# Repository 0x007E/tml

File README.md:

# `TML` - Temperature Logger

The `TML` is a board with an [LM386](#additional-information) that is used to scale up a temperature (0°-100°) from [KT200](#additional-information). The temperature gets A/D converted over an [ATtiny1606](#additional-information) and is stored in an eeprom [AT24CM0X](#additional-information) with current time and date that is provided by a [MCP7940](#additional-information) r(eal)-t(ime)-c(lock). The board itself provides a reverse polarity protection and can be supplied between `9-12V`. The voltage is line regulated to `5V`.

| Experience | Level |
|:------------|:-----:|
| Soldering   |  |

# Downloads

| Type      | File               | Description              |
|:---------:|:------------------:|:-------------------------|
| Schematic | [pdf](https://github.com/0x007E/tml/releases/latest/download/schematic.pdf) / [cadlab](https://cadlab.io/project/30575/main/files) | Schematic files |
| Board | [pdf](https://github.com/0x007E/tml/releases/latest/download/pcb.pdf) / [cadlab](https://cadlab.io/project/30575/main/files) | Board file |
| Drill | [pdf](https://github.com/0x007E/tml/releases/latest/download/drill.pdf) | Drill file |
| BoM | [xlsx](https://github.com/0x007E/tml/releases/latest/download/bom.xlsx) / [html](https://github.com/0x007E/tml/releases/latest/download/ibom.html)          | Bill of Material as Excel/interactive HTML |
| PCB    | [zip](https://github.com/0x007E/tml/releases/latest/download/kicad.zip) / [tar](https://github.com/0x007E/tml/releases/latest/download/kicad.tar.gz)    | KiCAD/Gerber/BoM/Drill files       |

# Hardware

The pcb is created with `KiCAD`. All files are built with `github actions` so that they are ready for a production environment.

## PCB

The circuit board is populated on both sides (Top, Bottom). The best way for soldering the `SMD` components is within a vapor phase soldering system and for the `THT` components with a standard soldering system.

### Top Layer

### Bottom Layer

# Additional Information

| Type  | Link                                                | Description                                   |
|:------|:---------------------------------------------------:|:----------------------------------------------|
| LM358 | [pdf](https://www.ti.com/lit/ds/symlink/lm358b.pdf) | Industry-Standard Dual Operational Amplifiers |
| KT200 | [pdf](https://rocelec.widen.net/view/pdf/qxp2nqwwr1/INFNS04262-1.pdf?t.download=true&u=5oefqw) | Silicon Temperature Sensors |
| ATtiny1606 | [pdf](https://ww1.microchip.com/downloads/en/DeviceDoc/ATtiny804-06-07-1604-06-07-DataSheet-DS40002312A.pdf) | tinyAVR® 0-series |
| AT24CM01 | [pdf](https://ww1.microchip.com/downloads/en/DeviceDoc/AT24CM01-I2C-Compatible-Two-Wire-Serial-EEPROM-Data-Sheet-20006170A.pdf) | I²C-Compatible (Two-Wire) Serial EEPROM 1‑Mbit (131,072 x 8) |
| AT24CM02 | [pdf](https://ww1.microchip.com/downloads/en/DeviceDoc/I%C2%B2C-Compatible-(Two-Wire)-Serial-EEPROM-2-Mbit-(262,144x8)-20006197B.pdf) | I²C-Compatible (Two-Wire) Serial EEPROM 2‑Mbit (262,144 x 8) |
| MCP7940 | [pdf](https://ww1.microchip.com/downloads/en/DeviceDoc/MCP7940M-Low-Cost%20I2C-RTCC-with-SRAM-20002292C.pdf) | Low-Cost I2C Real-Time Clock/Calendar with SRAM |

---

R. GAECHTER

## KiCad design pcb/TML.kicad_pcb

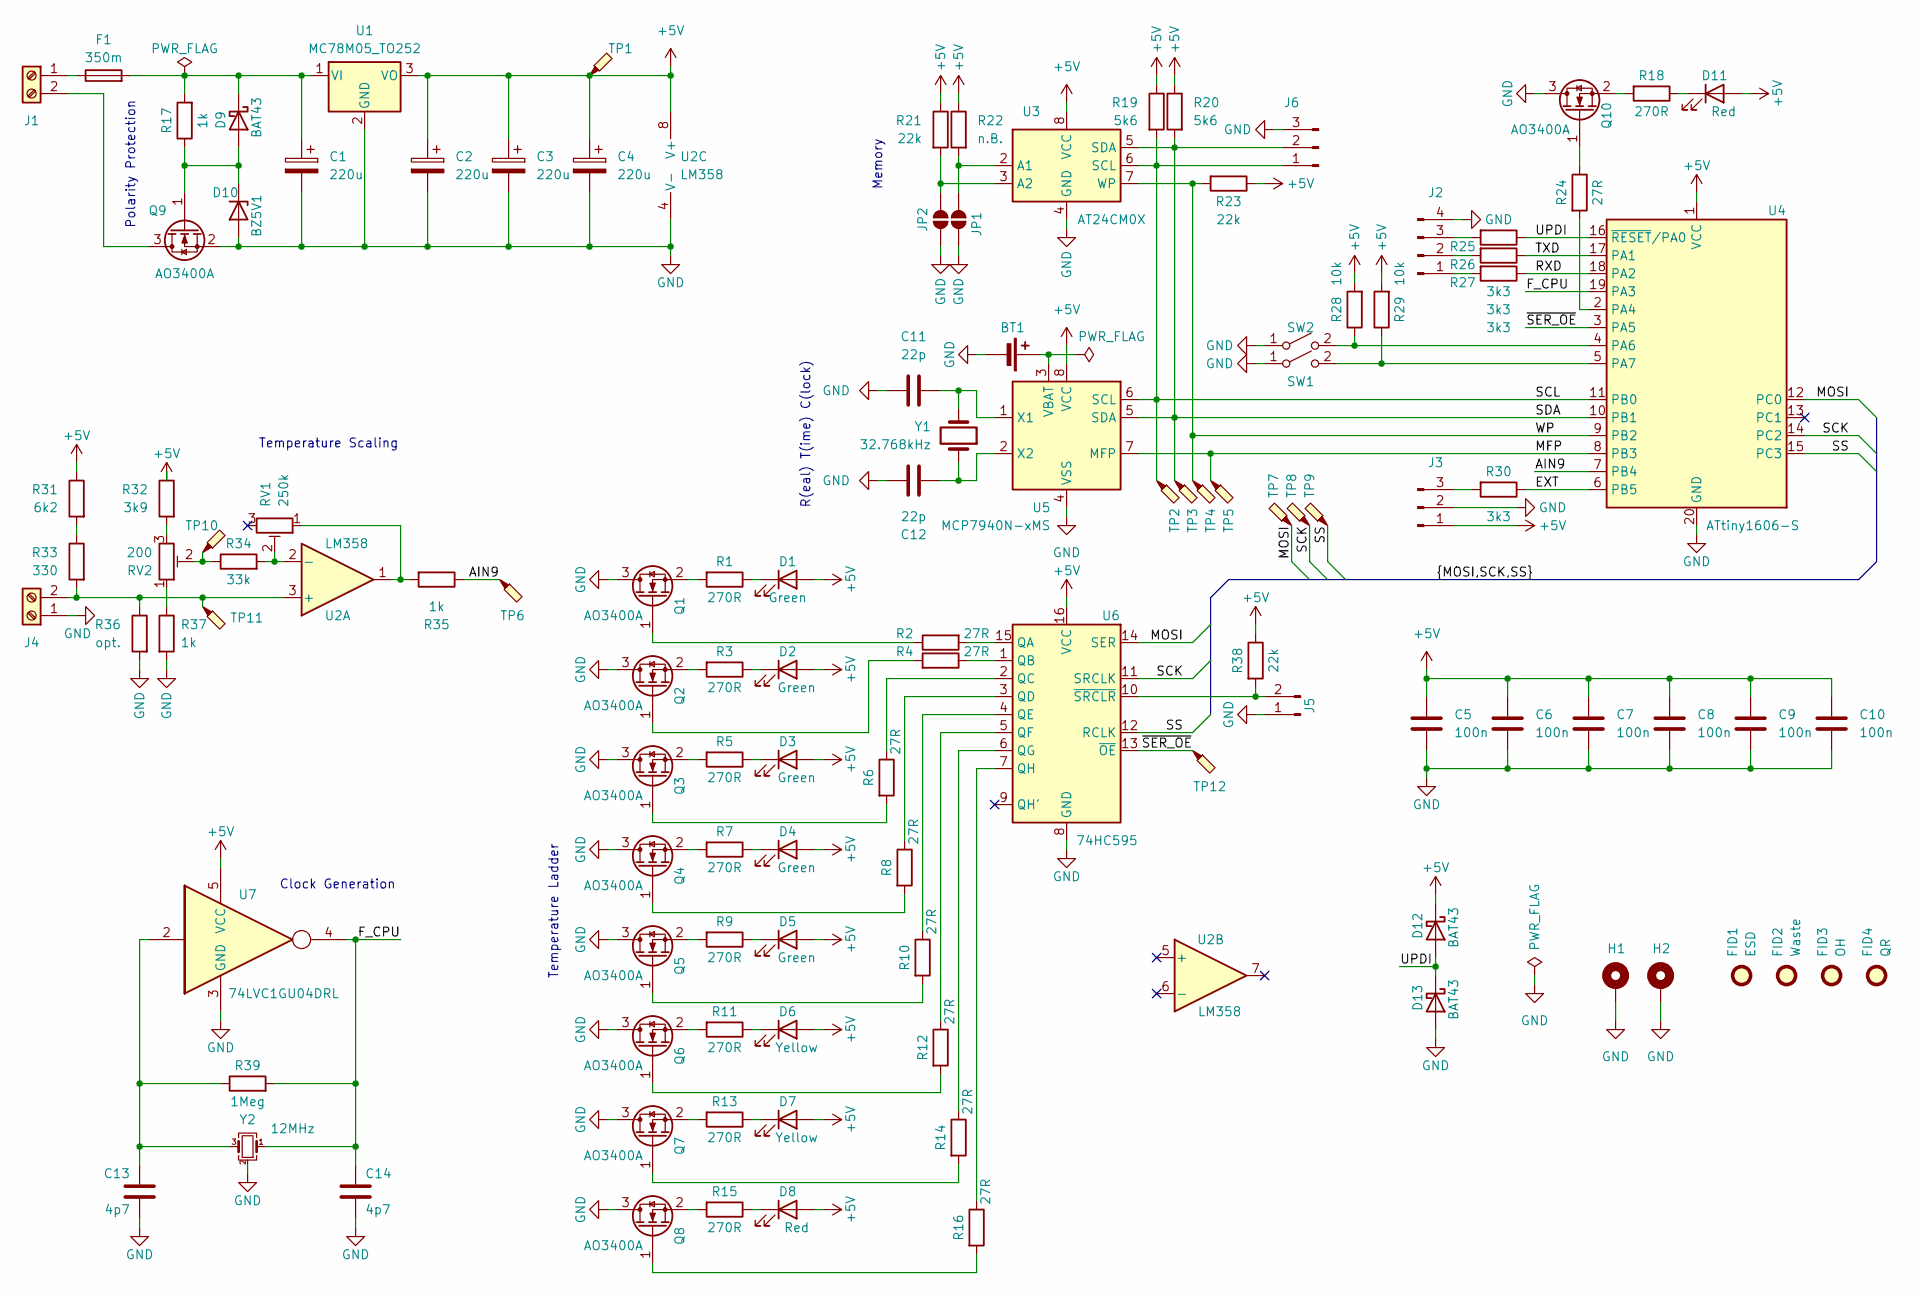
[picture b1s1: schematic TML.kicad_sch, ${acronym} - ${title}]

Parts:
BT1: Battery_Cell; BatteryHolder_LINX_BAT-HLD-012-SMT
C1, C2, C3, C4: 220u; CP_Radial_D8.0mm_P3.50mm
C5, C6, C7, C8, C9, C10: 100n; C_1206_3216Metric
C11, C12: 22p; C_1206_3216Metric
C13, C14: 4p7; C_1206_3216Metric
D1, D2, D3, D4, D5: Green; LED_D5.0mm
D6, D7: Yellow; LED_D5.0mm
D8: Red; LED_D5.0mm
D9, D12, D13: BAT43; D_MiniMELF
D10: BZ5V1; D_MiniMELF
D11: Red; LED_1206_3216Metric
F1: 350m; Fuse_1206_3216Metric
FID1: ESD; ESD-Logo_6.6x6mm_SilkScreen
FID2: Waste; WEEE-Logo_4.2x6mm_SilkScreen
FID3: OH; OSHW-Logo_5.7x6mm_SilkScreen
FID4: QR; QR_0x007e
H1, H2: MountingHole_Pad; MountingHole_3.2mm_M3_DIN965_Pad
J1, J4: Screw_Terminal_01x02; TerminalBlock_Phoenix_MKDS-1,5-2-5.08_1x02_P5.08mm_Horizont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
J2: Conn_01x04_Pin; PinHeader_1x04_P2.54mm_Vertical
J3, J6: Conn_01x03_Pin; PinHeader_1x03_P2.54mm_Vertical
J5: Conn_01x02_Pin; PinHeader_1x02_P2.54mm_Vertical
JP1, JP2: SolderJumper_2_Open; SolderJumper-2_P1.3mm_Open_RoundedPad1.0x1.5mm
Q1, Q2, Q3, Q4, Q5, Q6, Q7, Q8, Q9, Q10: AO3400A; SOT-23-3
R1, R3, R5, R7, R9, R11, R13, R15, R18: 270R; R_1206_3216Metric
R2, R4, R6, R8, R10, R12, R14, R16, R24: 27R; R_1206_3216Metric
R17, R35, R37: 1k; R_1206_3216Metric
R19, R20: 5k6; R_1206_3216Metric
R21, R23, R38: 22k; R_1206_3216Metric
R22: n.B.; R_1206_3216Metric
R25, R26, R27, R30: 3k3; R_1206_3216Metric
R28, R29: 10k; R_1206_3216Metric
R31: 6k2; R_1206_3216Metric
R32: 3k9; R_1206_3216Metric
R33: 330; R_1206_3216Metric
R34: 33k; R_1206_3216Metric
R36: opt.; R_1206_3216Metric
R39: 1Meg; R_1206_3216Metric
RV1: 250k; Potentiometer_Bourns_3296W_Vertical
RV2: 200; Potentiometer_Bourns_3296W_Vertical
SW1, SW2: SW_SPST; SW_PUSH_6mm
TP1, TP2, TP3, TP4, TP5, TP6, TP7, TP8, TP9, TP10, TP11, TP12: TestPoint_Probe; TestPoint_Pad_D1.5mm
U1: MC78M05_TO252; TO-252-2
U2: LM358; SOIC-8_3.9x4.9mm_P1.27mm
U3: AT24CM0X; SOIC-8_3.9x4.9mm_P1.27mm
U4: ATtiny1606-S; SOIC-20W_7.5x12.8mm_P1.27mm
U5: MCP7940N-xMS; SOIC-8_3.9x4.9mm_P1.27mm
U6: 74HC595; SOIC-16W_5.3x10.2mm_P1.27mm
U7: 74LVC1GU04DRL; SOT-553; DigiKey 296-18657-1-ND
Y1: 32.768kHz; Crystal_SMD_3215-2Pin_3.2x1.5mm
Y2: 12MHz; Crystal_SMD_Abracon_ABM8AIG-4Pin_3.2x2.5mm

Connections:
+5V: C2.1, C3.1, C4.1, C5.1, C6.1, C7.1, C8.1, C9.1, C10.1, D1.2 (A), D2.2 (A), D3.2 (A), D4.2 (A), D5.2 (A), D6.2 (A), D7.2 (A), D8.2 (A), D11.2 (A), D12.1 (K), J3.1, R19.1, R20.1, R21.1, R22.1, R23.1, R28.2, R29.2, R31.1, R32.1, R38.1, TP1.1, U1.3 (VO), U2.8 (V+), U3.8 (VCC), U4.1 (VCC), U5.8 (VCC), U6.16 (VCC), U7.5 (VCC)
/AIN9: R35.1, TP6.1, U4.7 (PB4)
/EXT: R30.1, U4.6 (PB5)
/F_CPU: C14.1, R39.2, U4.19 (PA3), U7.4, Y2.1
/MFP: TP5.1, U4.8 (PB3), U5.7 (MFP)
/MOSI: TP7.1, U4.12 (PC0), U6.14 (SER)
/RXD: R27.1, U4.18 (PA2)
/SCK: TP8.1, U4.14 (PC2), U6.11 (SRCLK)
/SCL: J6.1, R19.2, TP2.1, U3.6 (SCL), U4.11 (PB0), U5.6 (SCL)
/SDA: J6.2, R20.2, TP3.1, U3.5 (SDA), U4.10 (PB1), U5.5 (SDA)
/SS: TP9.1, U4.15 (PC3), U6.12 (RCLK)
/TXD: R26.1, U4.17 (PA1)
/UPDI: D12.2 (A), D13.1 (K), R25.1, U4.16 (~RESET/PA0)
/WP: R23.2, TP4.1, U3.7 (WP), U4.9 (PB2)
/~SER_OE: TP12.1, U4.3 (PA5), U6.13 (~OE)
GND: BT1.2 (-), C1.2, C2.2, C3.2, C4.2, C5.2, C6.2, C7.2, C8.2, C9.2, C10.2, C11.2, C12.2, C13.2, C14.2, D10.2 (A), D13.2 (A), H1.1, H2.1, J2.4, J3.2, J4.1, J5.1, J6.3, JP1.1 (A), JP2.1 (A), Q1.3 (D), Q2.3 (D), Q3.3 (D), Q4.3 (D), Q5.3 (D), Q6.3 (D), Q7.3 (D), Q8.3 (D), Q9.2 (S), Q10.3 (D), R36.2, R37.2, SW1.1 (A), SW2.1 (A), U1.2 (GND), U2.4 (V-), U3.4 (GND), U4.20 (GND), U5.4 (VSS), U6.8 (GND), U7.3 (GND), Y2.2 (G), Y2.4 (G)
unnamed: BT1.1 (+), U5.3 (VBAT)
unnamed: C13.1, R39.1, U7.2, Y2.3
unnamed: D1.1 (K), R1.1
unnamed: D2.1 (K), R3.1
unnamed: D3.1 (K), R5.1
unnamed: D4.1 (K), R7.1
unnamed: D5.1 (K), R9.1
unnamed: D6.1 (K), R11.1
unnamed: D7.1 (K), R13.1
unnamed: D8.1 (K), R15.1
unnamed: C1.1, D9.1 (K), F1.2, R17.2, U1.1 (VI)
unnamed: D9.2 (A), D10.1 (K), Q9.1 (G), R17.1
unnamed: D11.1 (K), R18.1
unnamed: F1.1, J1.1
unnamed: J1.2, Q9.3 (D)
unnamed: J2.1, R27.2
unnamed: J2.2, R26.2
unnamed: J2.3, R25.2
unnamed: J3.3, R30.2
unnamed: J4.2, R33.2, R36.1, TP11.1, U2.3 (+)
unnamed: J5.2, R38.2, U6.10 (~SRCLR)
unnamed: JP1.2 (B), R22.2, U3.2 (A1)
unnamed: JP2.2 (B), R21.2, U3.3 (A2)
unnamed: Q1.1 (G), R2.1
unnamed: Q1.2 (S), R1.2
unnamed: Q2.1 (G), R4.2
unnamed: Q2.2 (S), R3.2
unnamed: Q3.1 (G), R6.2
unnamed: Q3.2 (S), R5.2
unnamed: Q4.1 (G), R8.2
unnamed: Q4.2 (S), R7.2
unnamed: Q5.1 (G), R10.2
unnamed: Q5.2 (S), R9.2
unnamed: Q6.1 (G), R12.2
unnamed: Q6.2 (S), R11.2
unnamed: Q7.1 (G), R14.2
unnamed: Q7.2 (S), R13.2
unnamed: Q8.1 (G), R16.2
unnamed: Q8.2 (S), R15.2
unnamed: Q10.1 (G), R24.1
unnamed: Q10.2 (S), R18.2
unnamed: R31.2, R33.1
unnamed: R32.2, RV2.3
unnamed: R34.1, RV2.2, TP10.1
unnamed: R35.2, RV1.1, U2.1
unnamed: R37.1, RV2.1
unnamed: R29.1, SW1.2 (B), U4.5 (PA7)
unnamed: R28.1, SW2.2 (B), U4.4 (PA6)
unnamed: R34.2, RV1.2, U2.2 (-)
unnamed: R24.2, U4.2 (PA4)
unnamed: C11.1, U5.1 (X1), Y1.2
unnamed: C12.1, U5.2 (X2), Y1.1
unnamed: R2.2, U6.15 (QA)
unnamed: R4.1, U6.1 (QB)
unnamed: R6.1, U6.2 (QC)
unnamed: R8.1, U6.3 (QD)
unnamed: R10.1, U6.4 (QE)
unnamed: R12.1, U6.5 (QF)
unnamed: R14.1, U6.6 (QG)
unnamed: R16.1, U6.7 (QH)

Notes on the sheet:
Temperature Ladder
Memory
Polarity Protection
Temperature Scaling
R(eal) T(ime) C(lock)
Clock Generation

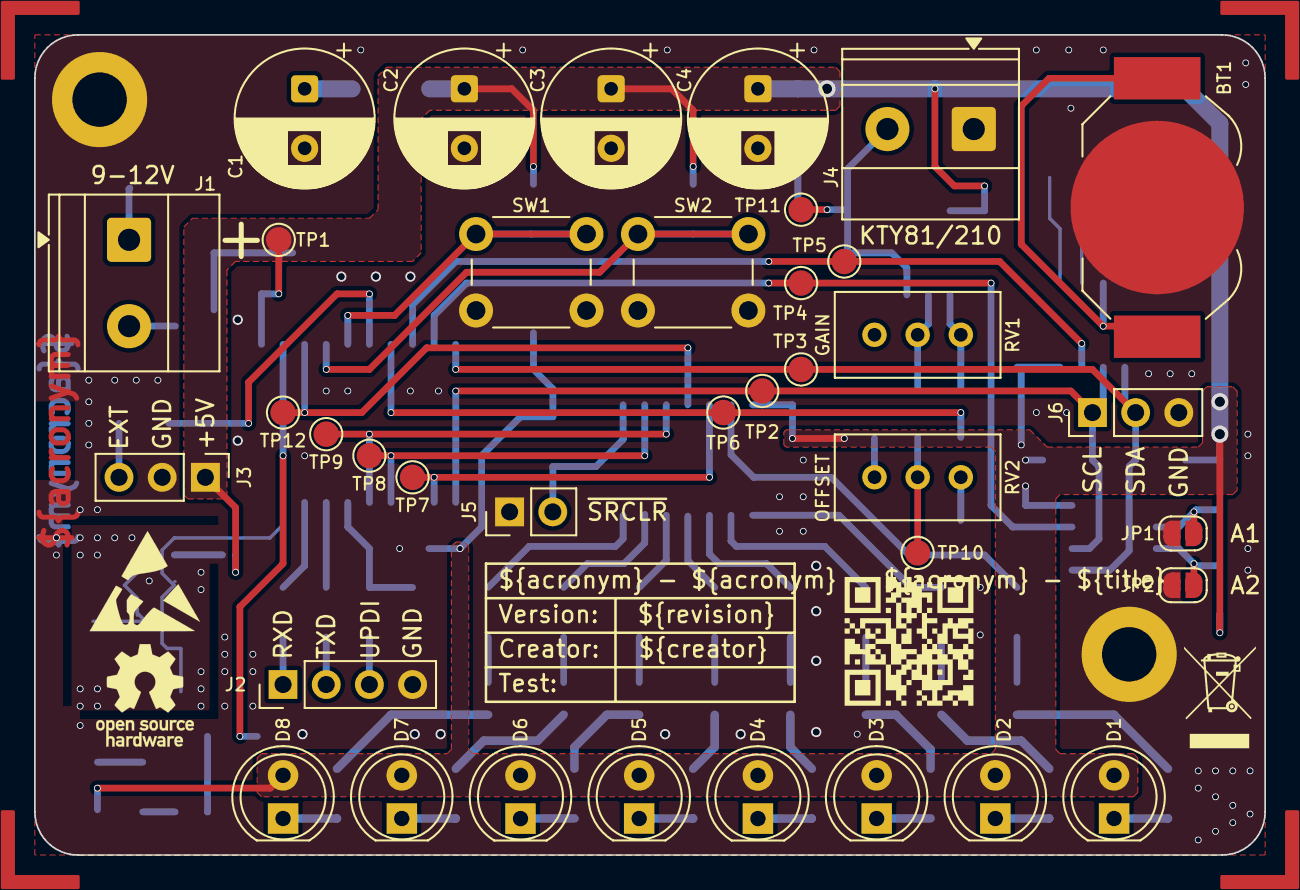
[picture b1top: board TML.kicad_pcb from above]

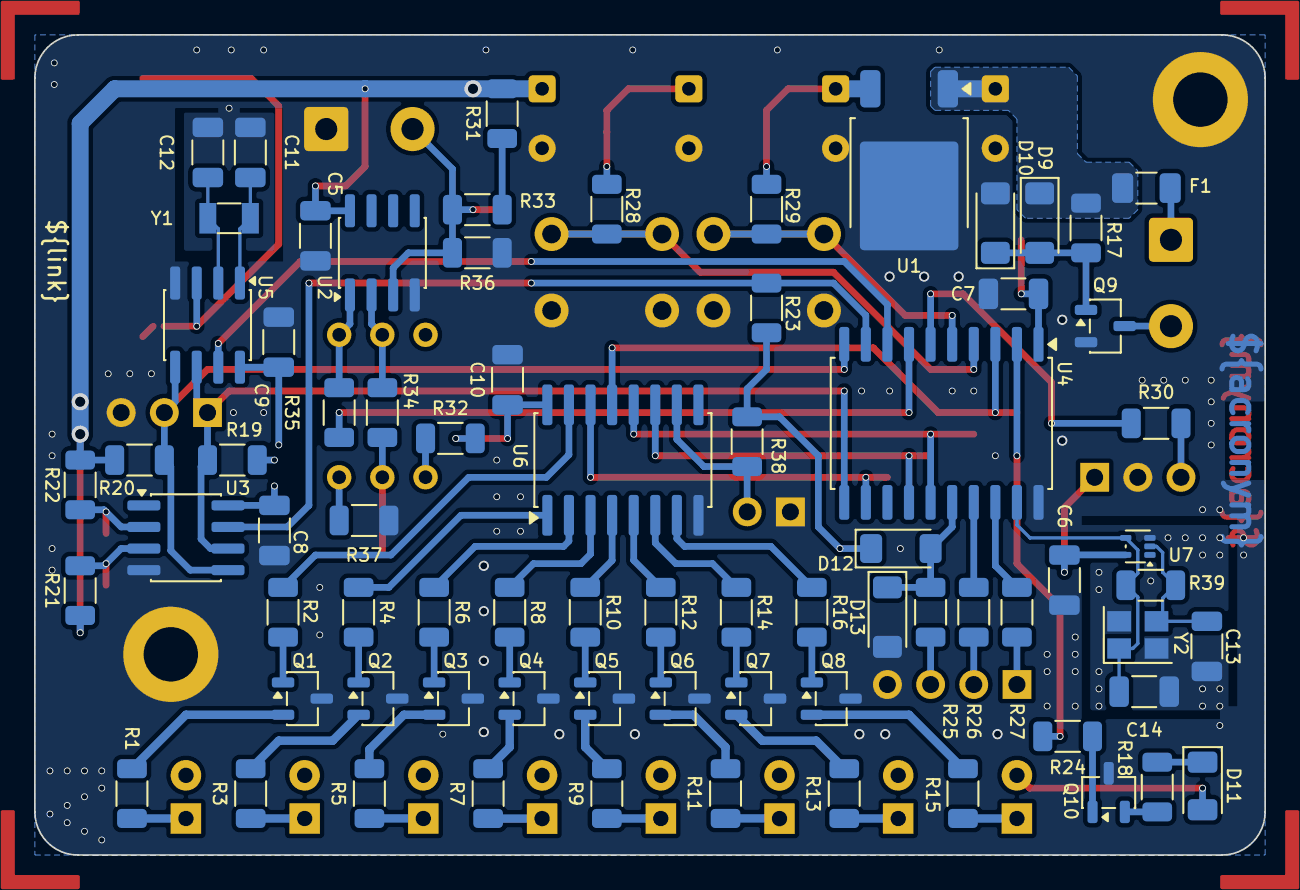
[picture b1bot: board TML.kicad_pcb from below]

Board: 2 copper layers, 72.4 x 48.3 mm, 117 parts (74 on the bottom side), 76 nets.

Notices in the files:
README.md:
License CC By-NC-SA
parts and their libraries:
license: CC BY-NC-SA 4.0
